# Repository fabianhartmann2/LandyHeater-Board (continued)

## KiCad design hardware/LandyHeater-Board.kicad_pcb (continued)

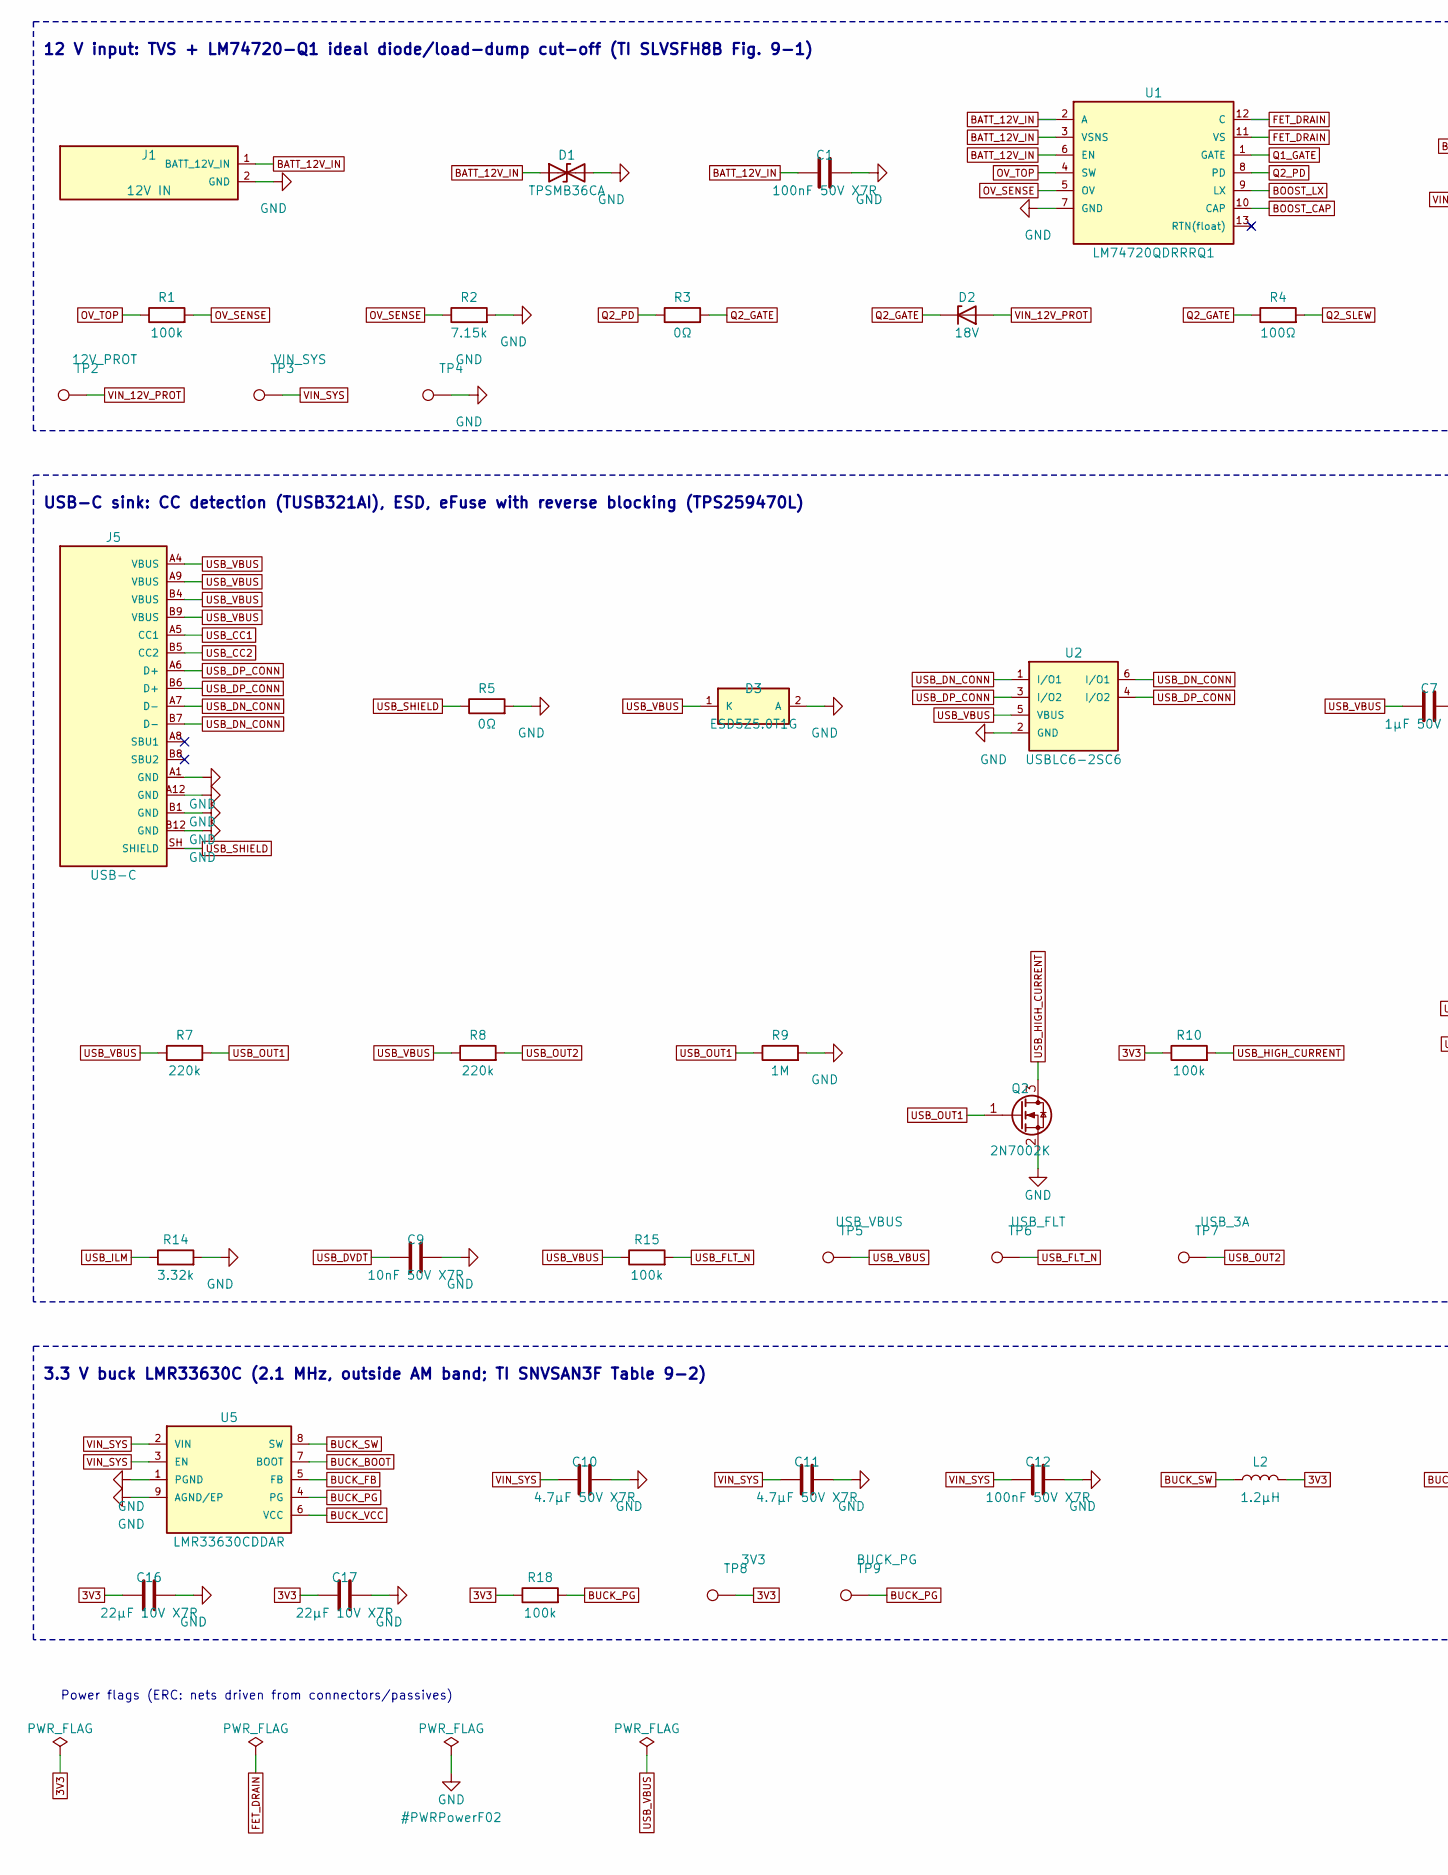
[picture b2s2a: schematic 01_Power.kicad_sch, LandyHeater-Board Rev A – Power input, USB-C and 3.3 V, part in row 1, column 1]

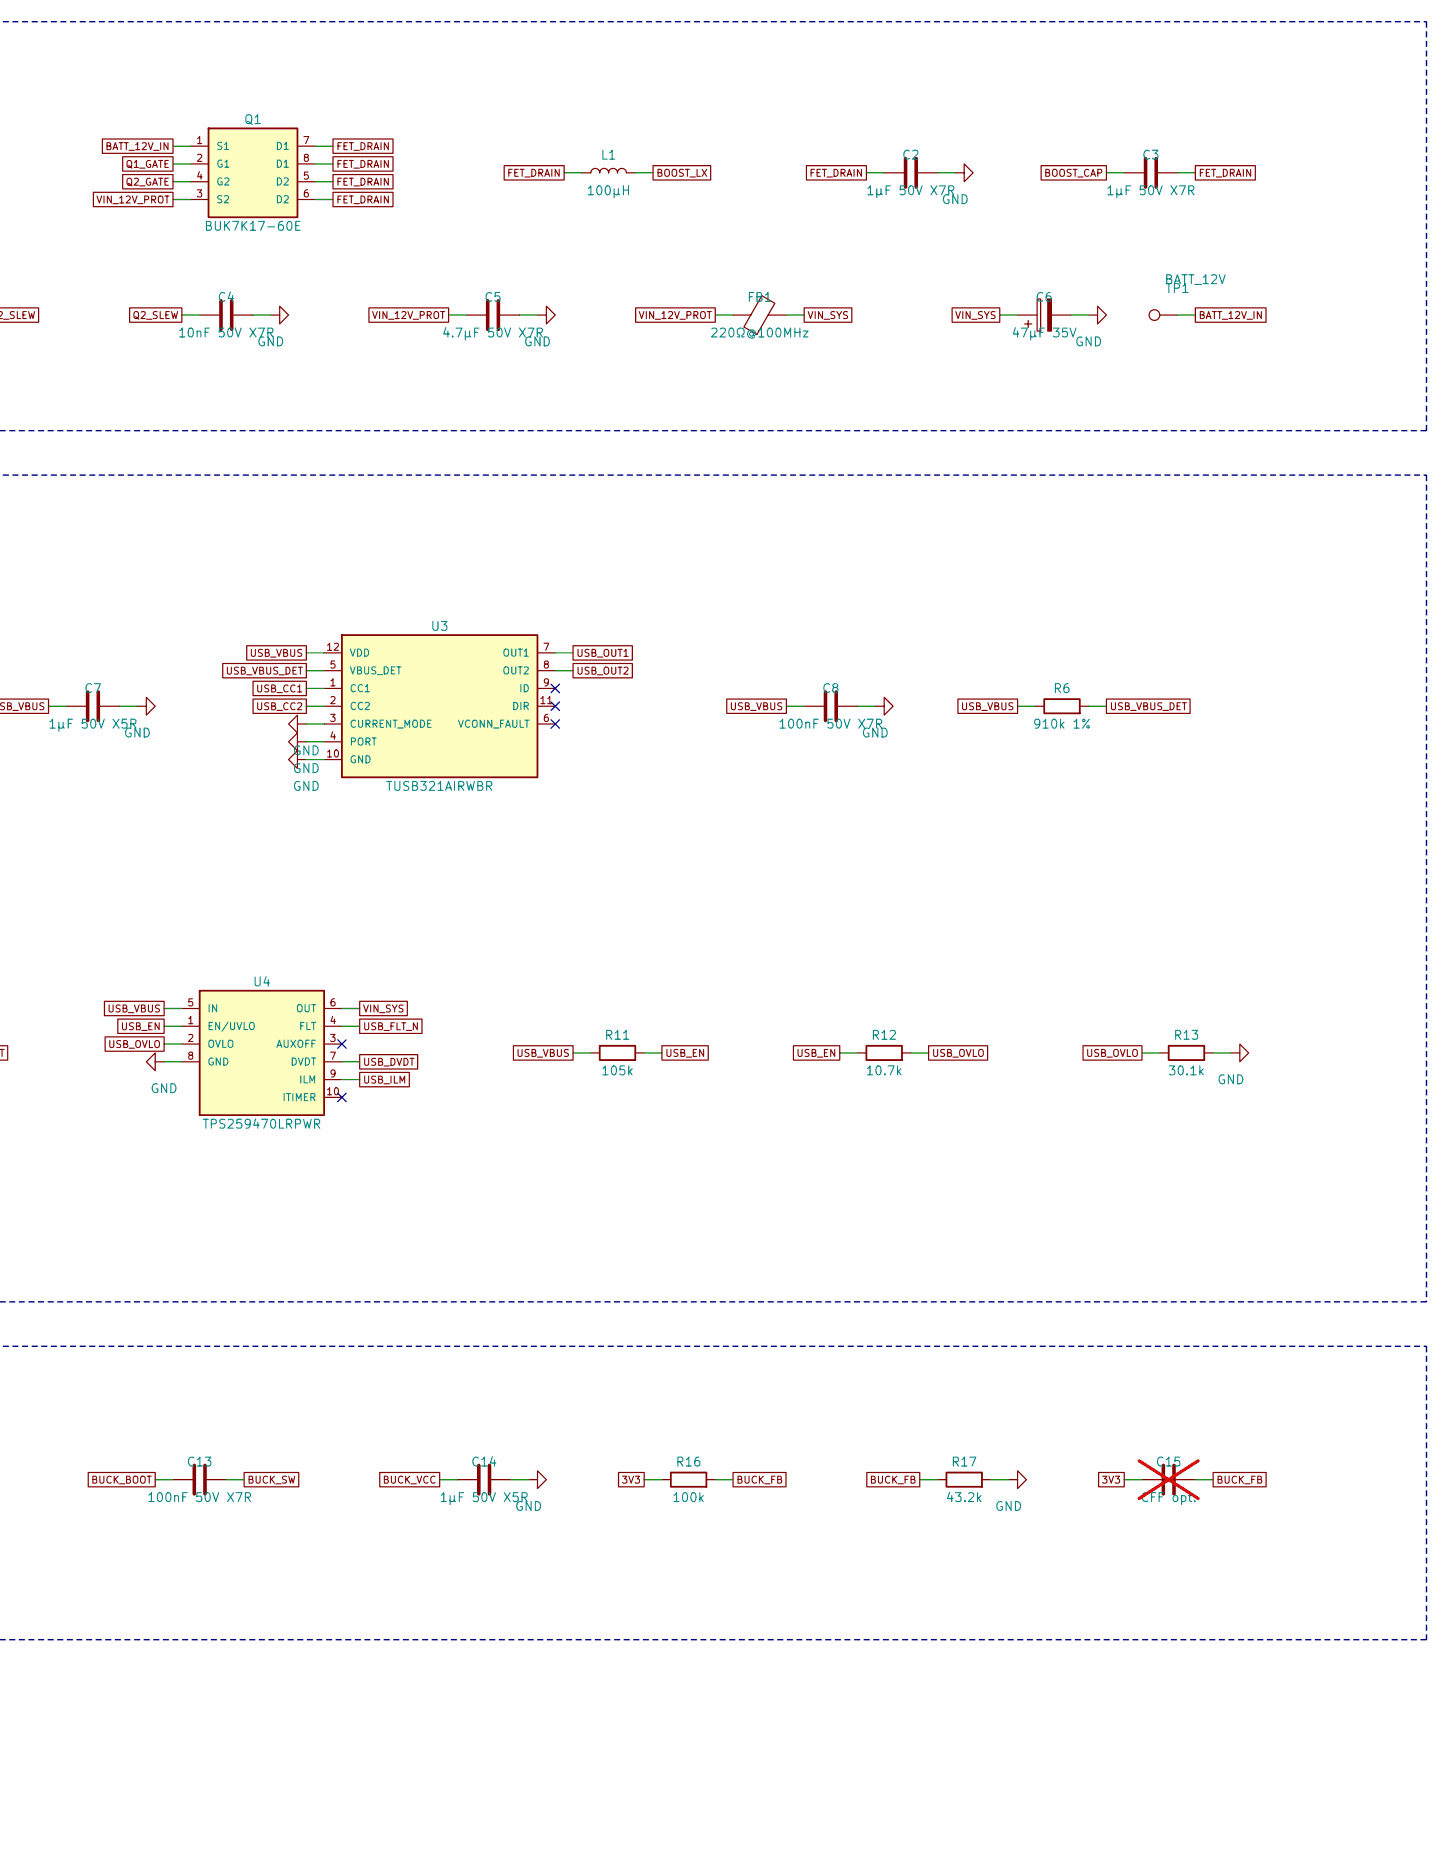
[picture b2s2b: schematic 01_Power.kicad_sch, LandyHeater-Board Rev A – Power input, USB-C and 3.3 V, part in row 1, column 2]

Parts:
C1, C8, C12, C13: 100nF 50V X7R; C_0603_1608Metric; MPN 0603B104K500NT; LCSC C30926
C2, C3: 1µF 50V X7R; C_0805_2012Metric; MPN CL21B105KBFNNNE; LCSC C28323
C4, C9: 10nF 50V X7R; C_0603_1608Metric; MPN 0603B103K500NT; LCSC C57112
C5, C11: 4.7µF 50V X7R; C_1206_3216Metric; MPN CL31B475KBHNNNE; LCSC C51205
C6: 47µF 35V; CP_Elec_6.3x7.7; MPN EEE-FK1V470P; LCSC C178565
C7, C14: 1µF 50V X5R; C_0603_1608Metric; MPN CL10A105KB8NNNC; LCSC C15849
C10: 4.7µF 50V X7R; C_1210_3225Metric; MPN GCJ32ER71H475KA12L; LCSC C417122
C15: CFF opt.; C_0603_1608Metric; not fitted
C16, C17: 22µF 10V X7R; C_1206_3216Metric; MPN GCJ31CR71A226KE01L; LCSC C6565118
D1: TPSMB36CA; D_SMB; MPN TPSMB36CA; LCSC C413569
D2: 18V; D_SOD-123; MPN SZMMSZ5248BT1G; LCSC C604812
D3: ESD5Z5.0T1G; D_SOD-523; MPN ESD5Z5.0T1G; LCSC C82044
FB1: 220Ω@100MHz; L_0805_2012Metric; MPN MPZ2012S221AT000; LCSC C76818
J1: 12V IN; Molex_Nano-Fit_105313-xx02_1x02_P2.50mm_Horizontal; MPN 1053131302; LCSC C17345480
J5: USB-C; USB_C_Receptacle_HRO_TYPE-C-31-M-12; MPN TYPE-C-31-M-12; LCSC C165948
L1: 100µH; L_APV_ANR3015; MPN ANR3015T101M; LCSC C6364791
L2: 1.2µH; L_Sunlord_MWSA0402S; MPN MMPC0402-1R2MT; LCSC C48579552
Q1: BUK7K17-60E; Nexperia_LFPAK56D_SOT1205; MPN BUK7K17-60EX; LCSC C478237
Q2: 2N7002K; SOT-23; MPN 2N7002K-7; LCSC C85047
R1, R10, R15, R16, R18: 100k; R_0603_1608Metric; MPN RC0603FR-07100KL; LCSC C14675
R2: 7.15k; R_0603_1608Metric; MPN 0603WAF7151T5E; LCSC C25980
R3, R5: 0Ω; R_0603_1608Metric; MPN 0603WAF0000T5E; LCSC C21189
R4: 100Ω; R_0603_1608Metric; MPN 0603WAF1000T5E; LCSC C22775
R6: 910k 1%; R_0603_1608Metric; MPN 0603WAF9103T5E; LCSC C23263
R7, R8: 220k; R_0603_1608Metric; MPN 0603WAF2203T5E; LCSC C22961
R9: 1M; R_0603_1608Metric; MPN 0603WAF1004T5E; LCSC C22935
R11: 105k; R_0603_1608Metric; MPN RC0603FR-07105KL; LCSC C141685
R12: 10.7k; R_0603_1608Metric; MPN 0603WAF1072T5E; LCSC C22857
R13: 30.1k; R_0603_1608Metric; MPN 0603WAF3012T5E; LCSC C23000
R14: 3.32k; R_0603_1608Metric; MPN RC0603FR-073K32L; LCSC C137731
R17: 43.2k; R_0603_1608Metric; MPN 0603WAF4322T5E; LCSC C23053
TP1: BATT_12V; TestPoint_Pad_D1.0mm
TP2: 12V_PROT; TestPoint_Pad_D1.0mm
TP3: VIN_SYS; TestPoint_Pad_D1.0mm
TP4: GND; TestPoint_Pad_D1.0mm
TP5: USB_VBUS; TestPoint_Pad_D1.0mm
TP6: USB_FLT; TestPoint_Pad_D1.0mm
TP7: USB_3A; TestPoint_Pad_D1.0mm
TP8: 3V3; TestPoint_Pad_D1.0mm
TP9: BUCK_PG; TestPoint_Pad_D1.0mm
U1: LM74720QDRRRQ1; TI_DRR0012F_WSON-12_3x3mm_RTN-float; MPN LM74720QDRRRQ1; LCSC C5219205
U2: USBLC6-2SC6; SOT-23-6; MPN USBLC6-2SC6; LCSC C7519
U3: TUSB321AIRWBR; Texas_X2QFN-12_1.6x1.6mm_P0.4mm; MPN TUSB321AIRWBR; LCSC C2674046
U4: TPS259470LRPWR; TI_RPW0010A_VQFN-HR-10_2x2mm; MPN TPS259470LRPWR; LCSC C3662793
U5: LMR33630CDDAR; Texas_HSOP-8-1EP_3.9x4.9mm_P1.27mm; MPN LMR33630CDDAR; LCSC C2071423

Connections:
3V3: C15.1, C16.1, C17.1, L2.2, R10.1, R16.1, R18.1, TP8.1; also elsewhere on the board
BATT_12V_IN: C1.1, D1.1 (A1), J1.1 (BATT_12V_IN), Q1.1 (S1), TP1.1, U1.2 (A), U1.3 (VSNS), U1.6 (EN)
BOOST_CAP: C3.1, U1.10 (CAP)
BOOST_LX: L1.2, U1.9 (LX)
BUCK_BOOT: C13.1, U5.7 (BOOT)
BUCK_FB: C15.2, R16.2, R17.1, U5.5 (FB)
BUCK_PG: R18.2, TP9.1, U5.4 (PG)
BUCK_SW: C13.2, L2.1, U5.8 (SW)
BUCK_VCC: C14.1, U5.6 (VCC)
FET_DRAIN: C2.1, C3.2, L1.1, Q1.5 (D2), Q1.6 (D2), Q1.7 (D1), Q1.8 (D1), U1.11 (VS), U1.12 (C)
GND: C1.2, C2.2, C4.2, C5.2, C6.2, C7.2, C8.2, C9.2, C10.2, C11.2, C12.2, C14.2, C16.2, C17.2, D1.2 (A2), D3.2 (A), J1.2 (GND), J5.A1 (GND), J5.A12 (GND), J5.B1 (GND), J5.B12 (GND), Q2.2 (S), R2.2, R5.2, R9.2, R13.2, R14.2, R17.2, TP4.1, U1.7 (GND), U2.2 (GND), U3.3 (CURRENT_MODE), U3.4 (PORT), U3.10 (GND), U4.8 (GND), U5.1 (PGND), U5.9 (AGND/EP); also elsewhere on the board
OV_SENSE: R1.2, R2.1, U1.5 (OV)
OV_TOP: R1.1, U1.4 (SW)
Q1_GATE: Q1.2 (G1), U1.1 (GATE)
Q2_GATE: D2.1 (K), Q1.4 (G2), R3.2, R4.1
Q2_PD: R3.1, U1.8 (PD)
Q2_SLEW: C4.1, R4.2
USB_CC1: J5.A5 (CC1), U3.1 (CC1)
USB_CC2: J5.B5 (CC2), U3.2 (CC2)
USB_DN_CONN: J5.A7 (D-), J5.B7 (D-), U2.1 (I/O1), U2.6 (I/O1); also elsewhere on the board
USB_DP_CONN: J5.A6 (D+), J5.B6 (D+), U2.3 (I/O2), U2.4 (I/O2); also elsewhere on the board
USB_DVDT: C9.1, U4.7 (DVDT)
USB_EN: R11.2, R12.1, U4.1 (EN/UVLO)
USB_FLT_N: R15.2, TP6.1, U4.4 (FLT)
USB_HIGH_CURRENT: Q2.3 (D), R10.2; also elsewhere on the board
USB_ILM: R14.1, U4.9 (ILM)
USB_OUT1: Q2.1 (G), R7.2, R9.1, U3.7 (OUT1)
USB_OUT2: R8.2, TP7.1, U3.8 (OUT2)
USB_OVLO: R12.2, R13.1, U4.2 (OVLO)
USB_SHIELD: J5.SH (SHIELD), R5.1
USB_VBUS: C7.1, C8.1, D3.1 (K), J5.A4 (VBUS), J5.A9 (VBUS), J5.B4 (VBUS), J5.B9 (VBUS), R6.1, R7.1, R8.1, R11.1, R15.1, TP5.1, U2.5 (VBUS), U3.12 (VDD), U4.5 (IN); also elsewhere on the board
USB_VBUS_DET: R6.2, U3.5 (VBUS_DET)
VIN_12V_PROT: C5.1, D2.2 (A), FB1.1, Q1.3 (S2), TP2.1; also elsewhere on the board
VIN_SYS: C6.1, C10.1, C11.1, C12.1, FB1.2, TP3.1, U4.6 (OUT), U5.2 (VIN), U5.3 (EN); also elsewhere on the board

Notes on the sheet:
12 V input: TVS + LM74720-Q1 ideal diode/load-dump cut-off (TI SLVSFH8B Fig. 9-1)
USB-C sink: CC detection (TUSB321AI), ESD, eFuse with reverse blocking (TPS259470L)
3.3 V buck LMR33630C (2.1 MHz, outside AM band; TI SNVSAN3F Table 9-2)
Power flags (ERC: nets driven from connectors/passives)

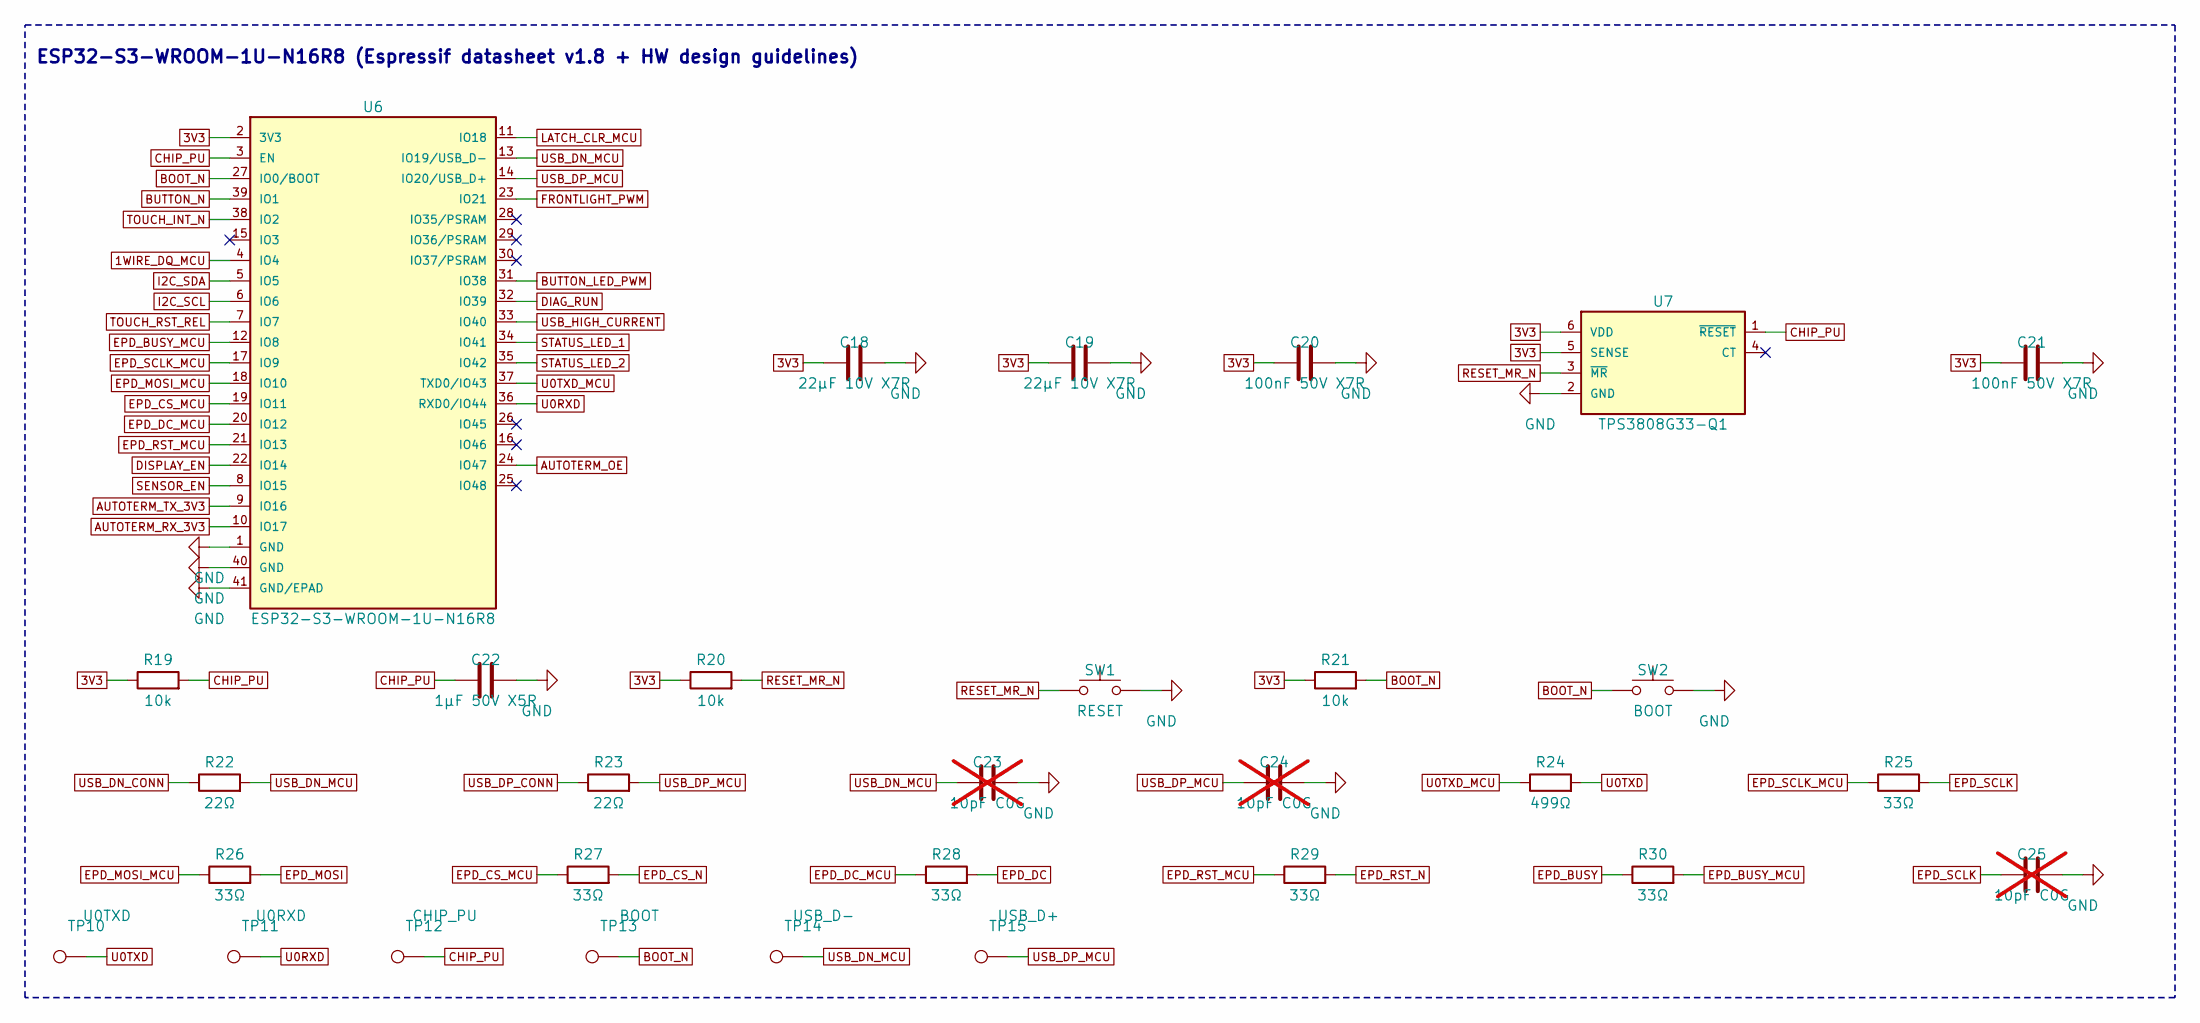
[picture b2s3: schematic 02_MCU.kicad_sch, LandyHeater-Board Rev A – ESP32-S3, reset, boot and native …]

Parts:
C18, C19: 22µF 10V X7R; C_1206_3216Metric; MPN GCJ31CR71A226KE01L; LCSC C6565118
C20, C21: 100nF 50V X7R; C_0603_1608Metric; MPN 0603B104K500NT; LCSC C30926
C22: 1µF 50V X5R; C_0603_1608Metric; MPN CL10A105KB8NNNC; LCSC C15849
C23, C24, C25: 10pF C0G; C_0603_1608Metric; MPN CL10C100JB8NNNC; LCSC C1634; not fitted
R19, R20, R21: 10k; R_0603_1608Metric; MPN RC0603FR-0710KL; LCSC C98220
R22, R23: 22Ω; R_0603_1608Metric; MPN 0603WAF220JT5E; LCSC C23345
R24: 499Ω; R_0603_1608Metric; MPN 0603WAF4990T5E; LCSC C23065
R25, R26, R27, R28, R29, R30: 33Ω; R_0603_1608Metric; MPN 0603WAF330JT5E; LCSC C23140
SW1: RESET; SW_Push_1P1T_XKB_TS-1187A; MPN TS-1187A-B-A-B; LCSC C318884
SW2: BOOT; SW_Push_1P1T_XKB_TS-1187A; MPN TS-1187A-B-A-B; LCSC C318884
TP10: U0TXD; TestPoint_Pad_D1.0mm
TP11: U0RXD; TestPoint_Pad_D1.0mm
TP12: CHIP_PU; TestPoint_Pad_D1.0mm
TP13: BOOT; TestPoint_Pad_D1.0mm
TP14: USB_D-; TestPoint_Pad_D1.0mm
TP15: USB_D+; TestPoint_Pad_D1.0mm
U6: ESP32-S3-WROOM-1U-N16R8; ESP32-S3-WROOM-1U; MPN ESP32-S3-WROOM-1U-N16R8; LCSC C3013946
U7: TPS3808G33-Q1; SOT-23-6; MPN TPS3808G33QDBVRQ1; LCSC C414616

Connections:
1WIRE_DQ_MCU: U6.4 (IO4); also elsewhere on the board
3V3: C18.1, C19.1, C20.1, C21.1, R19.1, R20.1, R21.1, U6.2 (3V3), U7.5 (SENSE), U7.6 (VDD); also elsewhere on the board
AUTOTERM_OE: U6.24 (IO47); also elsewhere on the board
AUTOTERM_RX_3V3: U6.10 (IO17); also elsewhere on the board
AUTOTERM_TX_3V3: U6.9 (IO16); also elsewhere on the board
BOOT_N: R21.2, SW2.1, TP13.1, U6.27 (IO0/BOOT)
BUTTON_LED_PWM: U6.31 (IO38); also elsewhere on the board
BUTTON_N: U6.39 (IO1); also elsewhere on the board
CHIP_PU: C22.1, R19.2, TP12.1, U6.3 (EN), U7.1 (~RESET)
DIAG_RUN: U6.32 (IO39); also elsewhere on the board
DISPLAY_EN: U6.22 (IO14); also elsewhere on the board
EPD_BUSY: R30.1; also elsewhere on the board
EPD_BUSY_MCU: R30.2, U6.12 (IO8)
EPD_CS_MCU: R27.1, U6.19 (IO11)
EPD_CS_N: R27.2; also elsewhere on the board
EPD_DC: R28.2; also elsewhere on the board
EPD_DC_MCU: R28.1, U6.20 (IO12)
EPD_MOSI: R26.2; also elsewhere on the board
EPD_MOSI_MCU: R26.1, U6.18 (IO10)
EPD_RST_MCU: R29.1, U6.21 (IO13)
EPD_RST_N: R29.2; also elsewhere on the board
EPD_SCLK: C25.1, R25.2; also elsewhere on the board
EPD_SCLK_MCU: R25.1, U6.17 (IO9)
FRONTLIGHT_PWM: U6.23 (IO21); also elsewhere on the board
GND: C18.2, C19.2, C20.2, C21.2, C22.2, C23.2, C24.2, C25.2, SW1.2, SW2.2, U6.1 (GND), U6.40 (GND), U6.41 (GND/EPAD), U7.2 (GND); also elsewhere on the board
I2C_SCL: U6.6 (IO6); also elsewhere on the board
I2C_SDA: U6.5 (IO5); also elsewhere on the board
LATCH_CLR_MCU: U6.11 (IO18); also elsewhere on the board
RESET_MR_N: R20.2, SW1.1, U7.3 (~MR)
SENSOR_EN: U6.8 (IO15); also elsewhere on the board
STATUS_LED_1: U6.34 (IO41); also elsewhere on the board
STATUS_LED_2: U6.35 (IO42); also elsewhere on the board
TOUCH_INT_N: U6.38 (IO2); also elsewhere on the board
TOUCH_RST_REL: U6.7 (IO7); also elsewhere on the board
U0RXD: TP11.1, U6.36 (RXD0/IO44)
U0TXD: R24.2, TP10.1
U0TXD_MCU: R24.1, U6.37 (TXD0/IO43)
USB_DN_CONN: R22.1; also elsewhere on the board
USB_DN_MCU: C23.1, R22.2, TP14.1, U6.13 (IO19/USB_D-)
USB_DP_CONN: R23.1; also elsewhere on the board
USB_DP_MCU: C24.1, R23.2, TP15.1, U6.14 (IO20/USB_D+)
USB_HIGH_CURRENT: U6.33 (IO40); also elsewhere on the board

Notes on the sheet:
ESP32-S3-WROOM-1U-N16R8 (Espressif datasheet v1.8 + HW design guidelines)

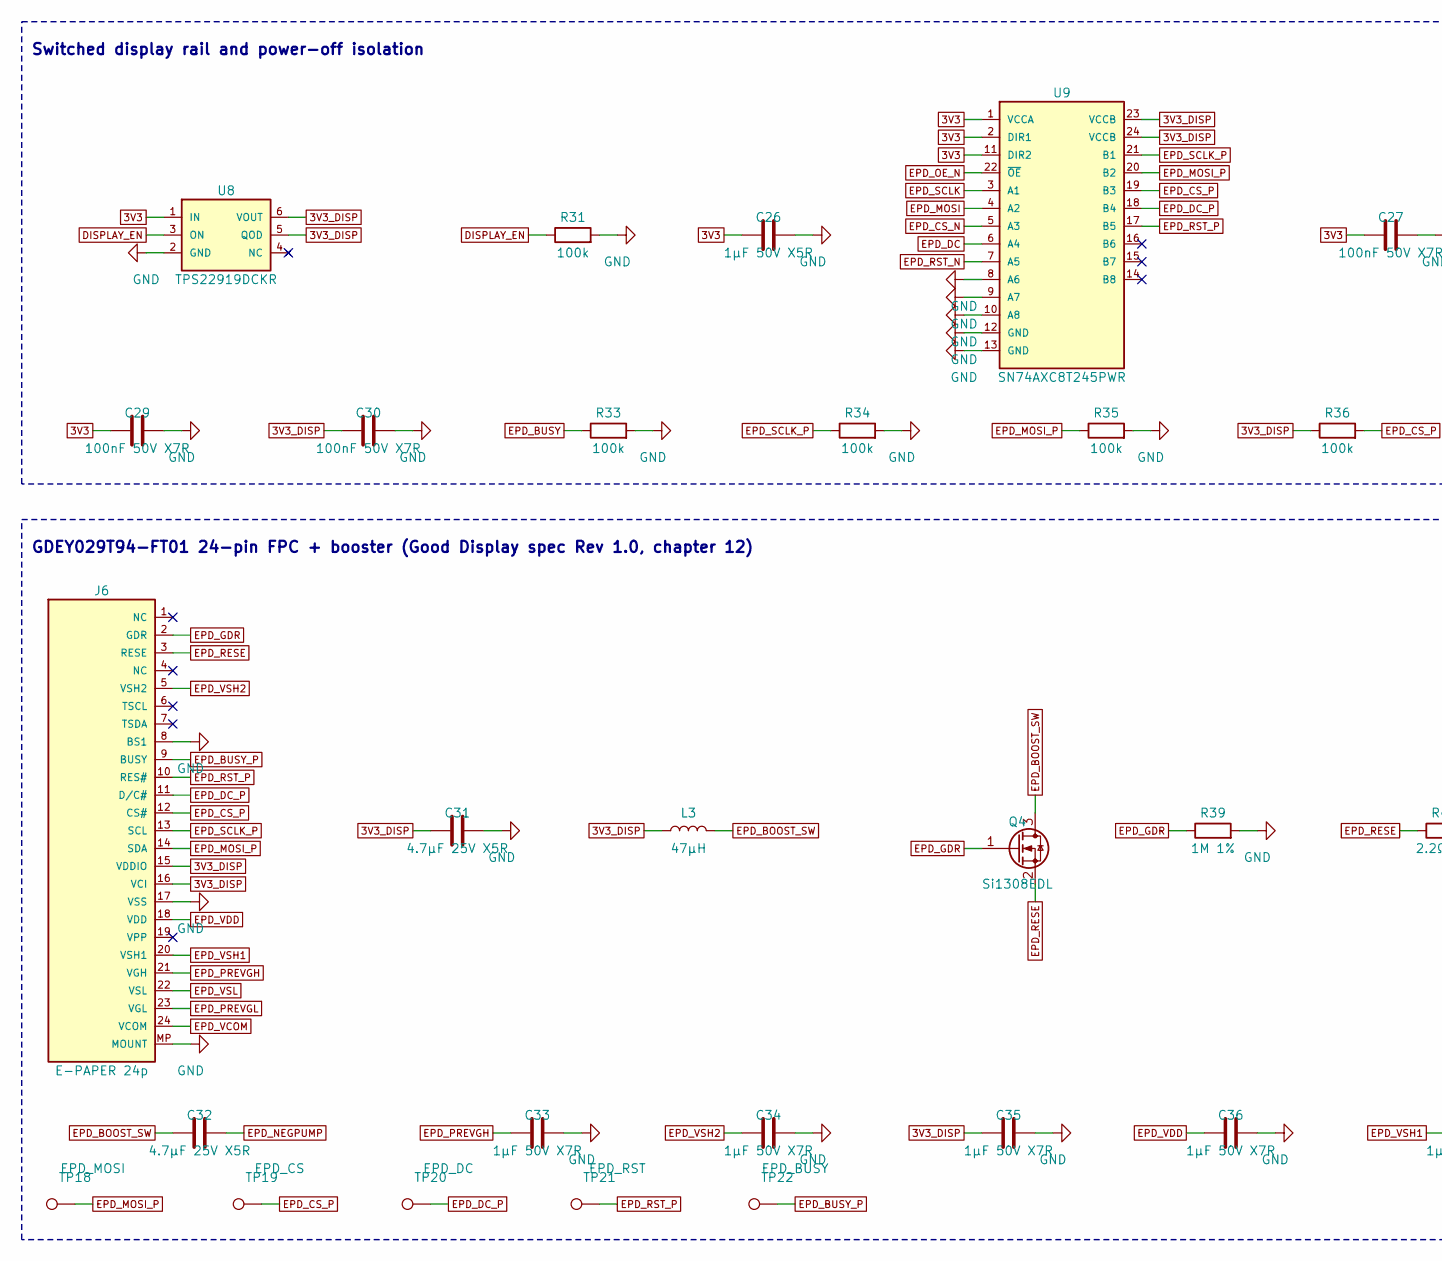
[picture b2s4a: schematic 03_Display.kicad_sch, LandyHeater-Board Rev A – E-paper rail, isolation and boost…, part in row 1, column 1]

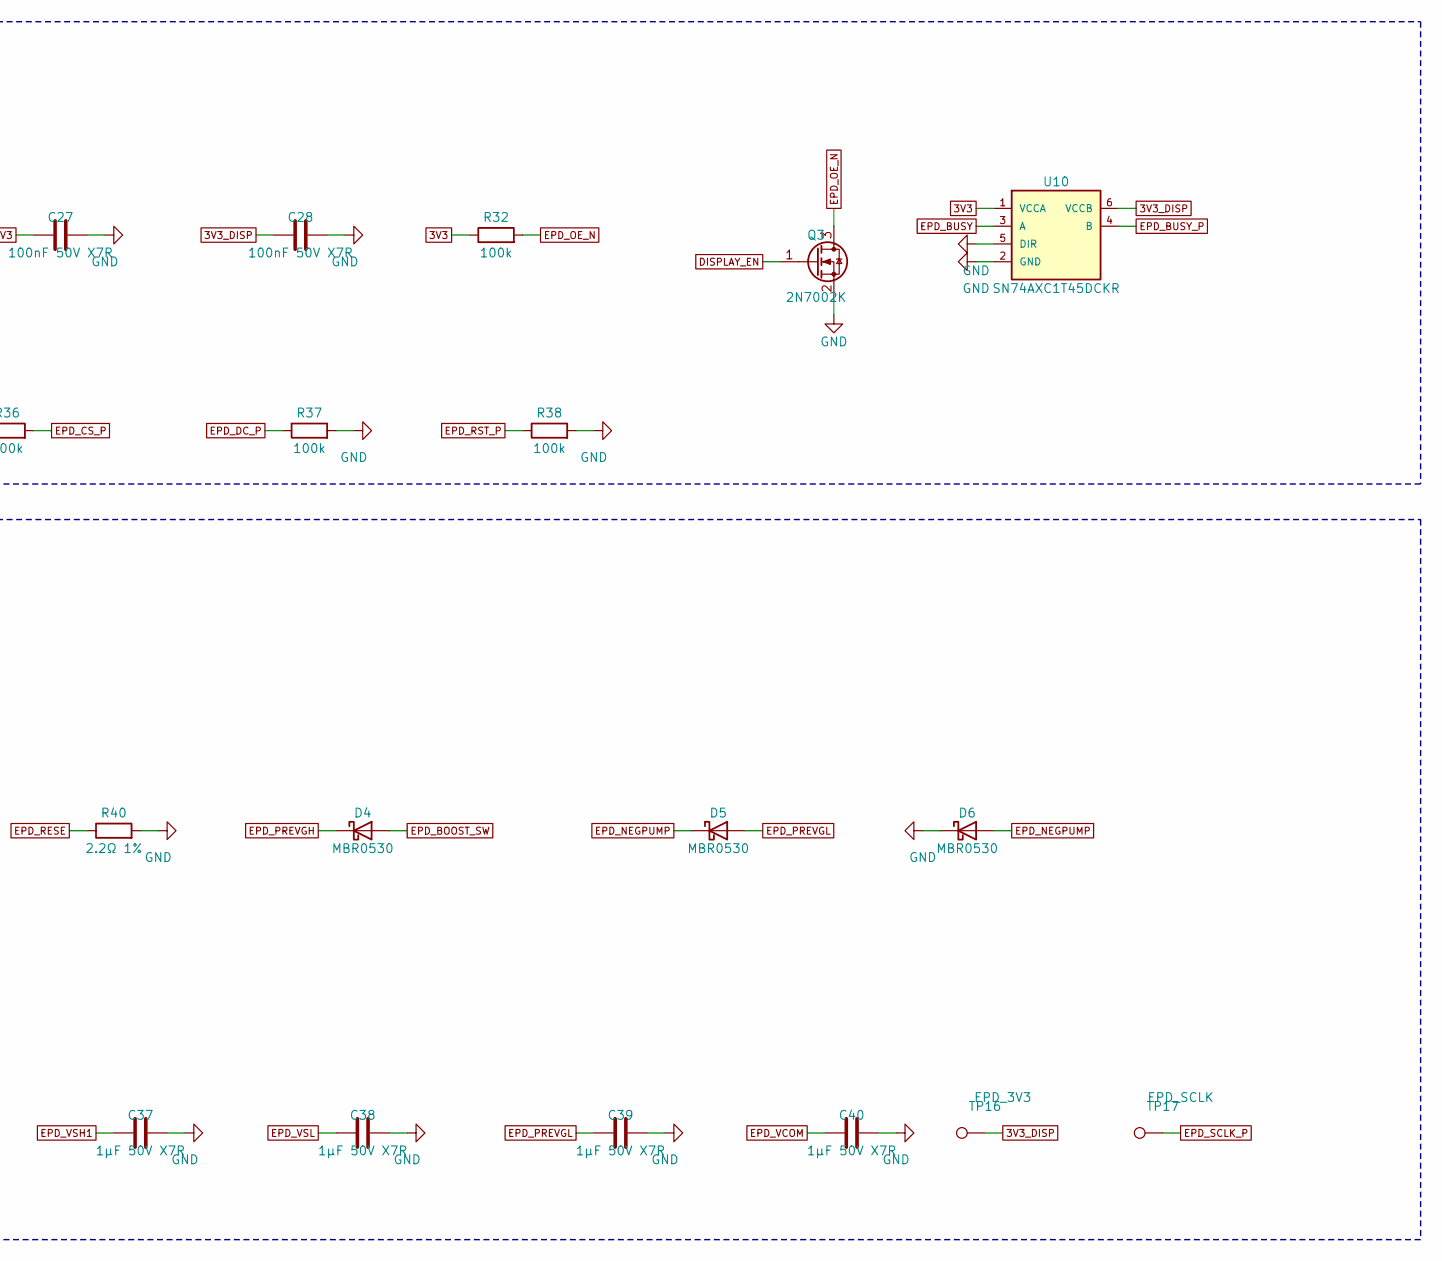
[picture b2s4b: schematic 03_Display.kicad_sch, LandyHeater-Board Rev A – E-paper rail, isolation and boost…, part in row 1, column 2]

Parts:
C26: 1µF 50V X5R; C_0603_1608Metric; MPN CL10A105KB8NNNC; LCSC C15849
C27, C28, C29, C30: 100nF 50V X7R; C_0603_1608Metric; MPN 0603B104K500NT; LCSC C30926
C31, C32: 4.7µF 25V X5R; C_0805_2012Metric; MPN CL21A475KAQNNNE; LCSC C1779
C33, C34, C35, C36, C37, C38, C39, C40: 1µF 50V X7R; C_0805_2012Metric; MPN CL21B105KBFNNNE; LCSC C28323
D4, D5, D6: MBR0530; D_SOD-123; MPN MBR0530-TP; LCSC C42388518
J6: E-PAPER 24p; Hirose_FH12-24S-0.5SH_1x24-1MP_P0.50mm_Horizontal; MPN FH12-24S-0.5SH(55); LCSC C202112
L3: 47µH; L_Taiyo-Yuden_NR-40xx; MPN NRS4018T470MDGJV; LCSC C5355142
Q3: 2N7002K; SOT-23; MPN 2N7002K-7; LCSC C85047
Q4: Si1308EDL; SOT-323_SC-70; MPN SI1308EDL-T1-GE3; LCSC C469327
R31, R32, R33, R34, R35, R36, R37, R38: 100k; R_0603_1608Metric; MPN RC0603FR-07100KL; LCSC C14675
R39: 1M 1%; R_0603_1608Metric; MPN 0603WAF1004T5E; LCSC C22935
R40: 2.2Ω 1%; R_0603_1608Metric; MPN RC0603FR-072R2L; LCSC C112307
TP16: EPD_3V3; TestPoint_Pad_D1.0mm
TP17: EPD_SCLK; TestPoint_Pad_D1.0mm
TP18: EPD_MOSI; TestPoint_Pad_D1.0mm
TP19: EPD_CS; TestPoint_Pad_D1.0mm
TP20: EPD_DC; TestPoint_Pad_D1.0mm
TP21: EPD_RST; TestPoint_Pad_D1.0mm
TP22: EPD_BUSY; TestPoint_Pad_D1.0mm
U8: TPS22919DCKR; SOT-363_SC-70-6; MPN TPS22919DCKR; LCSC C2149796
U9: SN74AXC8T245PWR; TSSOP-24_4.4x7.8mm_P0.65mm; MPN SN74AXC8T245PWR; LCSC C882718
U10: SN74AXC1T45DCKR; SOT-363_SC-70-6; MPN SN74AXC1T45DCKR; LCSC C2677392

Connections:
3V3: C26.1, C27.1, C29.1, R32.1, U8.1 (IN), U9.1 (VCCA), U9.2 (DIR1), U9.11 (DIR2), U10.1 (VCCA); also elsewhere on the board
3V3_DISP: C28.1, C30.1, C31.1, C35.1, J6.15 (VDDIO), J6.16 (VCI), L3.1, R36.1, TP16.1, U8.5 (QOD), U8.6 (VOUT), U9.23 (VCCB), U9.24 (VCCB), U10.6 (VCCB)
DISPLAY_EN: Q3.1 (G), R31.1, U8.3 (ON); also elsewhere on the board
EPD_BOOST_SW: C32.1, D4.2 (A), L3.2, Q4.3 (D)
EPD_BUSY: R33.1, U10.3 (A); also elsewhere on the board
EPD_BUSY_P: J6.9 (BUSY), TP22.1, U10.4 (B)
EPD_CS_N: U9.5 (A3); also elsewhere on the board
EPD_CS_P: J6.12 (CS#), R36.2, TP19.1, U9.19 (B3)
EPD_DC: U9.6 (A4); also elsewhere on the board
EPD_DC_P: J6.11 (D/C#), R37.1, TP20.1, U9.18 (B4)
EPD_GDR: J6.2 (GDR), Q4.1 (G), R39.1
EPD_MOSI: U9.4 (A2); also elsewhere on the board
EPD_MOSI_P: J6.14 (SDA), R35.1, TP18.1, U9.20 (B2)
EPD_NEGPUMP: C32.2, D5.1 (K), D6.2 (A)
EPD_OE_N: Q3.3 (D), R32.2, U9.22 (~OE)
EPD_PREVGH: C33.1, D4.1 (K), J6.21 (VGH)
EPD_PREVGL: C39.1, D5.2 (A), J6.23 (VGL)
EPD_RESE: J6.3 (RESE), Q4.2 (S), R40.1
EPD_RST_N: U9.7 (A5); also elsewhere on the board
EPD_RST_P: J6.10 (RES#), R38.1, TP21.1, U9.17 (B5)
EPD_SCLK: U9.3 (A1); also elsewhere on the board
EPD_SCLK_P: J6.13 (SCL), R34.1, TP17.1, U9.21 (B1)
EPD_VCOM: C40.1, J6.24 (VCOM)
EPD_VDD: C36.1, J6.18 (VDD)
EPD_VSH1: C37.1, J6.20 (VSH1)
EPD_VSH2: C34.1, J6.5 (VSH2)
EPD_VSL: C38.1, J6.22 (VSL)
GND: C26.2, C27.2, C28.2, C29.2, C30.2, C31.2, C33.2, C34.2, C35.2, C36.2, C37.2, C38.2, C39.2, C40.2, D6.1 (K), J6.8 (BS1), J6.17 (VSS), J6.MP (MOUNT), Q3.2 (S), R31.2, R33.2, R34.2, R35.2, R37.2, R38.2, R39.2, R40.2, U8.2 (GND), U9.8 (A6), U9.9 (A7), U9.10 (A8), U9.12 (GND), U9.13 (GND), U10.2 (GND), U10.5 (DIR); also elsewhere on the board

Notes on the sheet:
Switched display rail and power-off isolation
GDEY029T94-FT01 24-pin FPC + booster (Good Display spec Rev 1.0, chapter 12)
